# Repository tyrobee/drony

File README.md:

# Droney
Drone designed using dRehmflight vtol system with a payload dropping 

#PCB
Made a pcb for the dRehmflight (https://github.com/nickrehm/dRehmFlight)

-Schematics

-Design

#Firmware
I created it from the from the dRehmflight manual available in the dRehmflight repo and the i left the comments for each and every loop and function to make it easy for everyone to understand.
#Cad
The frame is designed around the famous dji f450 frame which is reliable and strong.
 -Arm

-Top Plate

-Bottom Plate

#Bom

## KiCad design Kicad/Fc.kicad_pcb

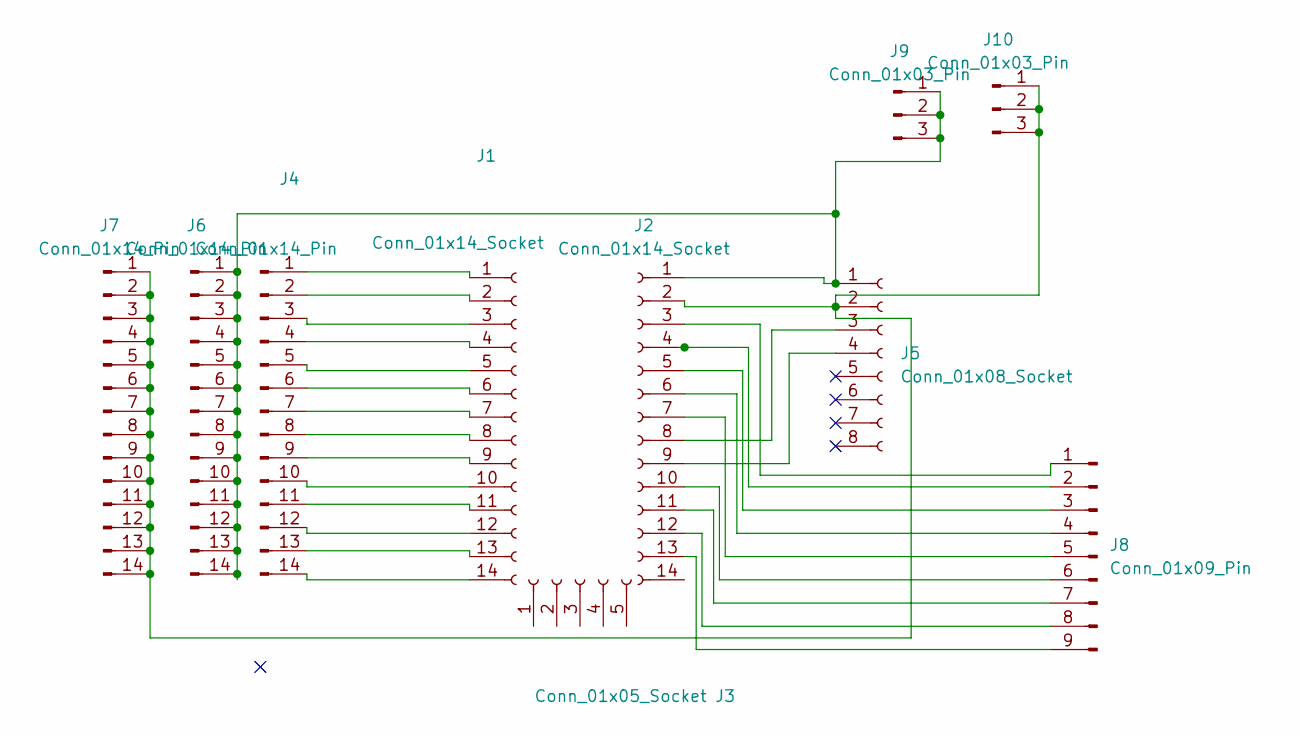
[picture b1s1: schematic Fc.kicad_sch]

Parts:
J1, J2: Conn_01x14_Socket; PinSocket_1x14_P2.54mm_Vertical
J3: Conn_01x05_Socket; PinSocket_1x05_P2.54mm_Vertical
J4, J6, J7: Conn_01x14_Pin; PinHeader_1x14_P2.54mm_Vertical
J5: Conn_01x08_Socket; PinSocket_1x08_P2.54mm_Vertical
J8: Conn_01x09_Pin; PinHeader_1x09_P2.54mm_Vertical
J9, J10: Conn_01x03_Pin; PinHeader_1x03_P2.54mm_Vertical

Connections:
unnamed: J1.1, J4.1
unnamed: J1.2, J4.2
unnamed: J1.3, J4.3
unnamed: J1.4, J4.4
unnamed: J1.5, J4.5
unnamed: J1.6, J4.6
unnamed: J1.7, J4.7
unnamed: J1.8, J4.8
unnamed: J1.9, J4.9
unnamed: J1.10, J4.10
unnamed: J1.11, J4.11
unnamed: J1.12, J4.12
unnamed: J1.13, J4.13
unnamed: J1.14, J4.14
unnamed: J2.1, J5.1, J6.1, J6.2, J6.3, J6.4, J6.5, J6.6, J6.7, J6.8, J6.9, J6.10, J6.11, J6.12, J6.13, J6.14, J9.1, J9.2, J9.3
unnamed: J2.3, J8.1
unnamed: J2.4, J8.2
unnamed: J2.5, J8.3
unnamed: J2.6, J8.4
unnamed: J2.7, J8.5
unnamed: J2.8, J5.3
unnamed: J2.9, J5.4
unnamed: J2.10, J8.6
unnamed: J2.11, J8.7
unnamed: J2.12, J8.8
unnamed: J2.13, J8.9
unnamed: J2.2, J5.2, J7.1, J7.2, J7.3, J7.4, J7.5, J7.6, J7.7, J7.8, J7.9, J7.10, J7.11, J7.12, J7.13, J7.14, J10.1, J10.2, J10.3

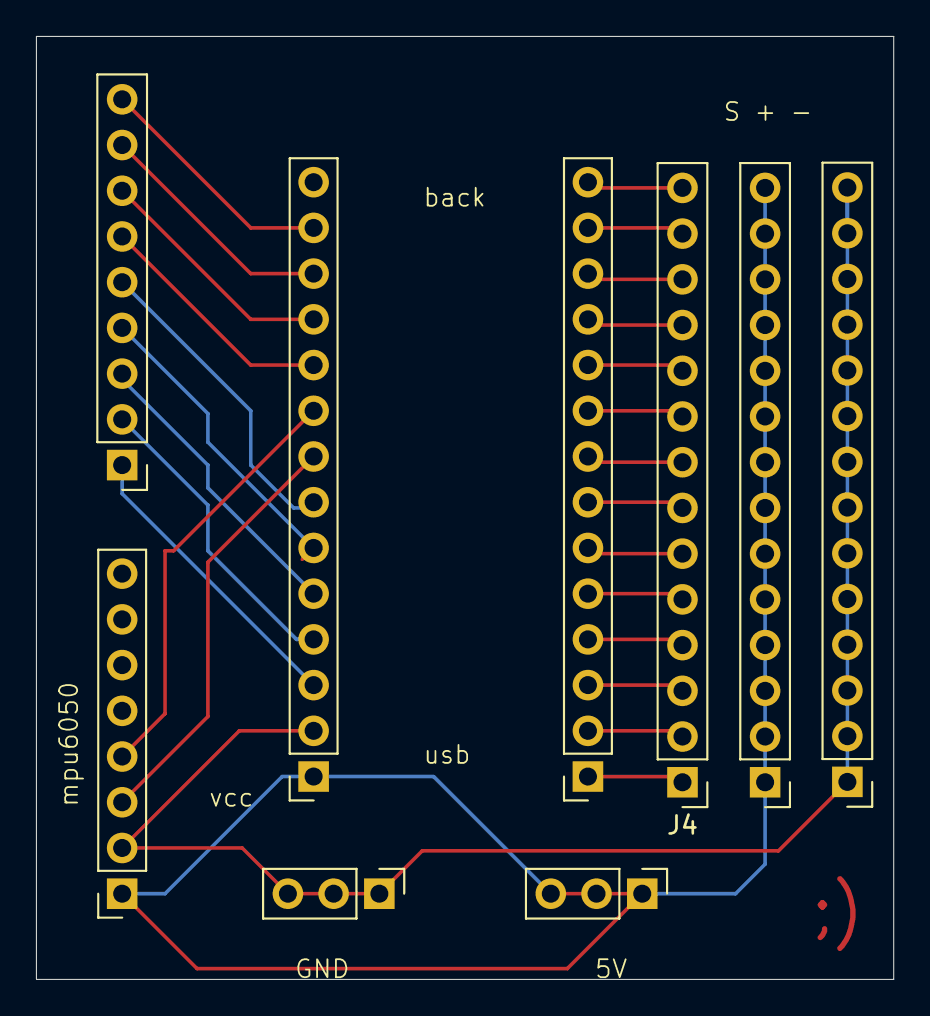
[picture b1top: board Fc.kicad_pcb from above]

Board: 2 copper layers, 47.6 x 52.4 mm, 9 parts (0 on the bottom side), 27 nets.

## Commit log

2026-01-08 Add initial firmware and KiCad files
2026-01-08 Expand README with PCB, Firmware, CAD, and BOM sections
    Added detailed sections for PCB, Firmware, CAD, and BOM with images.
2026-01-08 Correct capitalization of project name in README
